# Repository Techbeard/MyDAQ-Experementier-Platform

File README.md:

# MyDAQ-Experementier-Platform
Studentisches Projekt mit dme MY DAQ

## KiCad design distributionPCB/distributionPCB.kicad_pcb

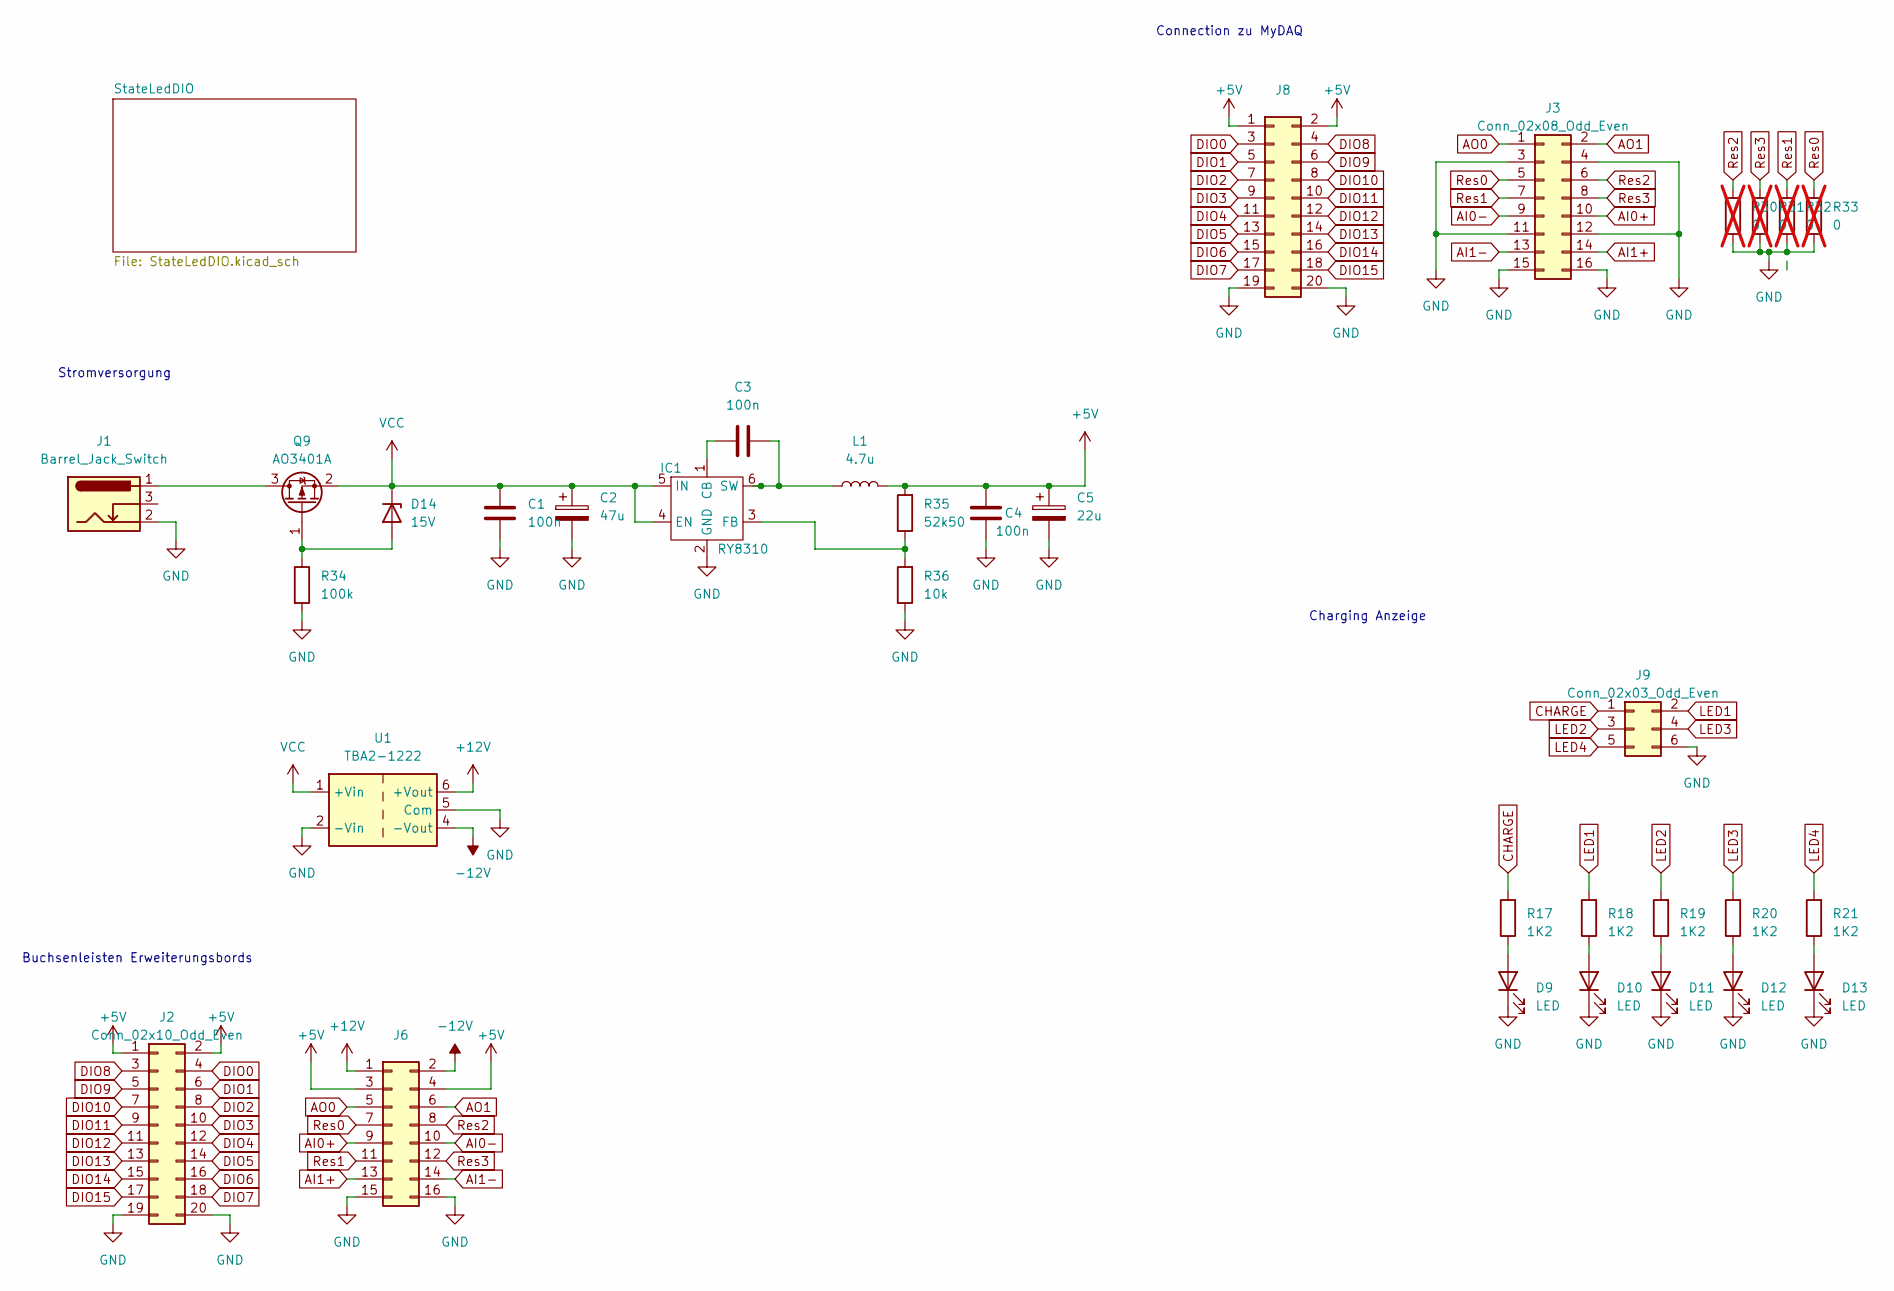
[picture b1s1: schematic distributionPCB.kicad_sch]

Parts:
C1, C3, C4: 100n; C_0402_1005Metric
C2: 47u; CP_Elec_5x5.4
C5: 22u; CP_Elec_5x5.4
D9, D10, D11, D12, D13: LED; LED_0805_2012Metric
D14: 15V; D_0402_1005Metric
IC1: RY8310; SOT-23-6
J1: Barrel_Jack_Switch; BarrelJack_10A
J2: Conn_02x10_Odd_Even; PinSocket_2x10_P2.54mm_Vertical
J3: Conn_02x08_Odd_Even; IDC-Header_2x08_P2.54mm_Vertical_SMD
J6: Conn_02x08_Odd_Even; PinSocket_2x08_P2.54mm_Vertical
J8: Conn_02x10_Odd_Even; IDC-Header_2x10_P2.54mm_Vertical_SMD
J9: Conn_02x03_Odd_Even; IDC-Header_2x03_P2.54mm_Vertical_SMD
L1: 4.7u; L_0630
Q9: AO3401A; SOT-23
R17, R18, R19, R20, R21: 1K2; R_0603_1608Metric
R30, R31, R32, R33: 0; R_0603_1608Metric; not fitted
R34: 100k; R_0402_1005Metric
R35: 52k50; R_0402_1005Metric
R36: 10k; R_0402_1005Metric
U1: TBA2-1222; Converter_DCDC_TRACO_TBA2-xxxx_Dual_THT

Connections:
+5V: C4.1, C5.1, J2.1, J2.2, J6.3, J6.4, J8.1, J8.2, L1.2, R35.2; also elsewhere on the board
+12V: J6.1, U1.6 (+Vout)
-12V: J6.2, U1.4 (-Vout)
AI0+: J3.10, J6.9
AI0-: J3.9, J6.10
AI1+: J3.14, J6.13
AI1-: J3.13, J6.14
AO0: J3.1, J6.5
AO1: J3.2, J6.6
CHARGE: J9.1, R17.2
DIO0: J2.4, J8.3; also elsewhere on the board
DIO1: J2.6, J8.5; also elsewhere on the board
DIO2: J2.8, J8.7; also elsewhere on the board
DIO3: J2.10, J8.9; also elsewhere on the board
DIO4: J2.12, J8.11; also elsewhere on the board
DIO5: J2.14, J8.13; also elsewhere on the board
DIO6: J2.16, J8.15; also elsewhere on the board
DIO7: J2.18, J8.17; also elsewhere on the board
DIO8: J2.3, J8.4
DIO9: J2.5, J8.6
DIO10: J2.7, J8.8
DIO11: J2.9, J8.10
DIO12: J2.11, J8.12
DIO13: J2.13, J8.14
DIO14: J2.15, J8.16
DIO15: J2.17, J8.18
GND: C1.2, C2.2, C4.2, C5.2, D9.1 (K), D10.1 (K), D11.1 (K), D12.1 (K), D13.1 (K), IC1.2 (GND), J1.2, J2.19, J2.20, J3.3, J3.4, J3.11, J3.12, J3.15, J3.16, J6.15, J6.16, J8.19, J8.20, J9.6, R30.1, R31.1, R32.1, R33.1, R34.2, R36.1, U1.2 (-Vin), U1.5 (Com); also elsewhere on the board
LED1: J9.2, R18.2
LED2: J9.3, R19.2
LED3: J9.4, R20.2
LED4: J9.5, R21.2
unnamed: D9.2 (A), R17.1
unnamed: D10.2 (A), R18.1
unnamed: D11.2 (A), R19.1
unnamed: D12.2 (A), R20.1
unnamed: D13.2 (A), R21.1
unnamed: D14.2 (A), Q9.1 (G), R34.1
unnamed: C3.1, IC1.1 (CB)
unnamed: IC1.3 (FB), R35.1, R36.2
unnamed: C3.2, IC1.6 (SW), L1.1
unnamed: J1.1, Q9.3 (D)
Res0: J3.5, J6.7, R33.2
Res1: J3.7, J6.11, R32.2
Res2: J3.6, J6.8, R30.2
Res3: J3.8, J6.12, R31.2
VCC: C1.1, C2.1, D14.1 (K), IC1.4 (EN), IC1.5 (IN), Q9.2 (S), U1.1 (+Vin)

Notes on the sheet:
Buchsenleisten Erweiterungsbords
Stromversorgung
Charging Anzeige
Connection zu MyDAQ

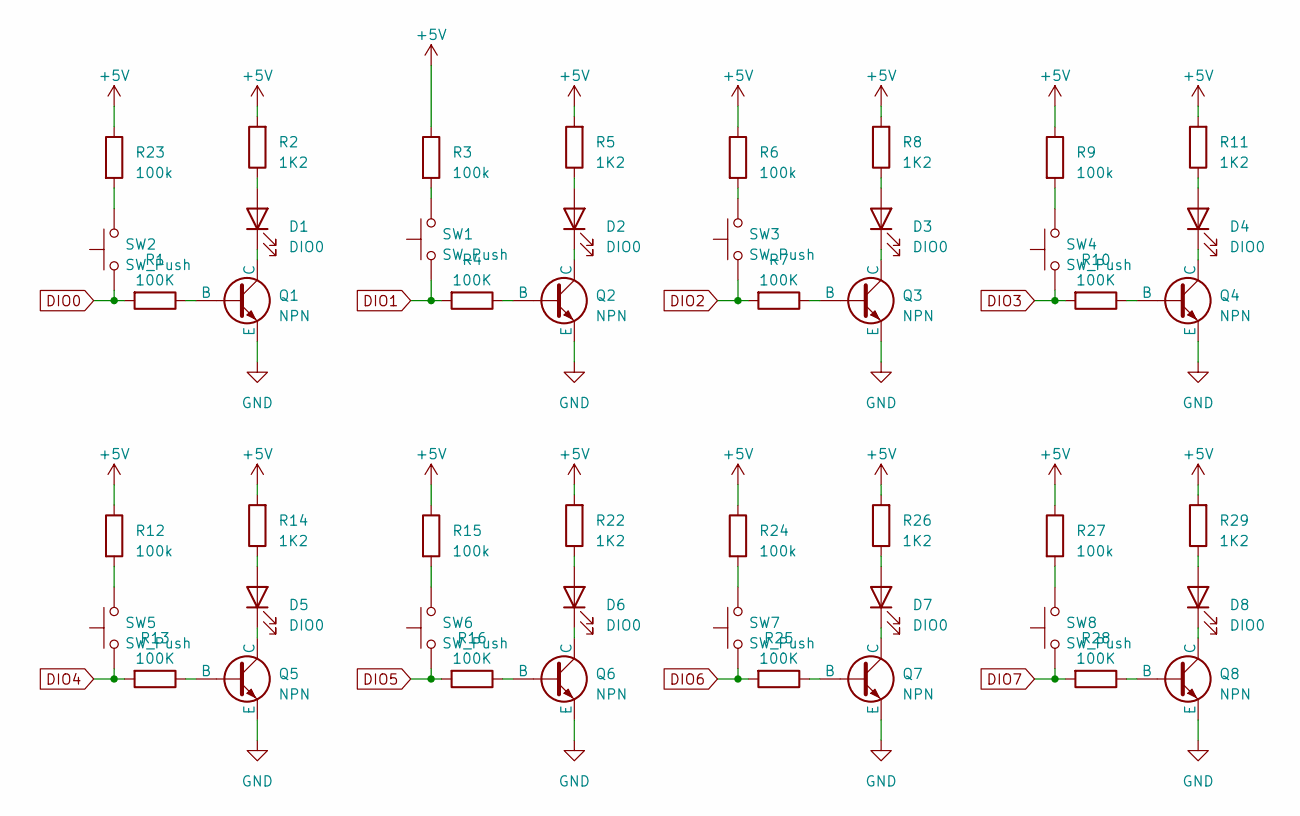
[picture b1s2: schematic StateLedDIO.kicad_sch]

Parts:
D1, D2, D3, D4, D5, D6, D7, D8: DIO0; LED_0805_2012Metric
Q1, Q2, Q3, Q4, Q5, Q6, Q7, Q8: NPN; TSOT-23
R1, R4, R7, R10, R13, R16, R25, R28: 100K; R_0603_1608Metric
R2, R5, R8, R11, R14, R22, R26, R29: 1K2; R_0603_1608Metric
R3, R6, R9, R12, R15, R23, R24, R27: 100k; R_0603_1608Metric
SW1, SW2, SW3, SW4, SW5, SW6, SW7, SW8: SW_Push; SW_SPST_SKQG_WithStem

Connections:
+5V: R2.2, R3.1, R5.2, R6.1, R8.2, R9.1, R11.2, R12.1, R14.2, R15.1, R22.2, R23.1, R24.1, R26.2, R27.1, R29.2; also elsewhere on the board
DIO0: R1.2, SW2.1; also elsewhere on the board
DIO1: R4.2, SW1.1; also elsewhere on the board
DIO2: R7.2, SW3.1; also elsewhere on the board
DIO3: R10.2, SW4.1; also elsewhere on the board
DIO4: R13.2, SW5.1; also elsewhere on the board
DIO5: R16.2, SW6.1; also elsewhere on the board
DIO6: R25.2, SW7.1; also elsewhere on the board
DIO7: R28.2, SW8.1; also elsewhere on the board
GND: Q1.3 (E), Q2.3 (E), Q3.3 (E), Q4.3 (E), Q5.3 (E), Q6.3 (E), Q7.3 (E), Q8.3 (E); also elsewhere on the board
unnamed: D1.2 (A), R2.1
unnamed: D1.1 (K), Q1.1 (C)
unnamed: D2.2 (A), R5.1
unnamed: D2.1 (K), Q2.1 (C)
unnamed: D3.2 (A), R8.1
unnamed: D3.1 (K), Q3.1 (C)
unnamed: D4.2 (A), R11.1
unnamed: D4.1 (K), Q4.1 (C)
unnamed: D5.2 (A), R14.1
unnamed: D5.1 (K), Q5.1 (C)
unnamed: D6.2 (A), R22.1
unnamed: D6.1 (K), Q6.1 (C)
unnamed: D7.2 (A), R26.1
unnamed: D7.1 (K), Q7.1 (C)
unnamed: D8.2 (A), R29.1
unnamed: D8.1 (K), Q8.1 (C)
unnamed: Q1.2 (B), R1.1
unnamed: Q2.2 (B), R4.1
unnamed: Q3.2 (B), R7.1
unnamed: Q4.2 (B), R10.1
unnamed: Q5.2 (B), R13.1
unnamed: Q6.2 (B), R16.1
unnamed: Q7.2 (B), R25.1
unnamed: Q8.2 (B), R28.1
unnamed: R3.2, SW1.2
unnamed: R6.2, SW3.2
unnamed: R9.2, SW4.2
unnamed: R12.2, SW5.2
unnamed: R15.2, SW6.2
unnamed: R23.2, SW2.2
unnamed: R24.2, SW7.2
unnamed: R27.2, SW8.2

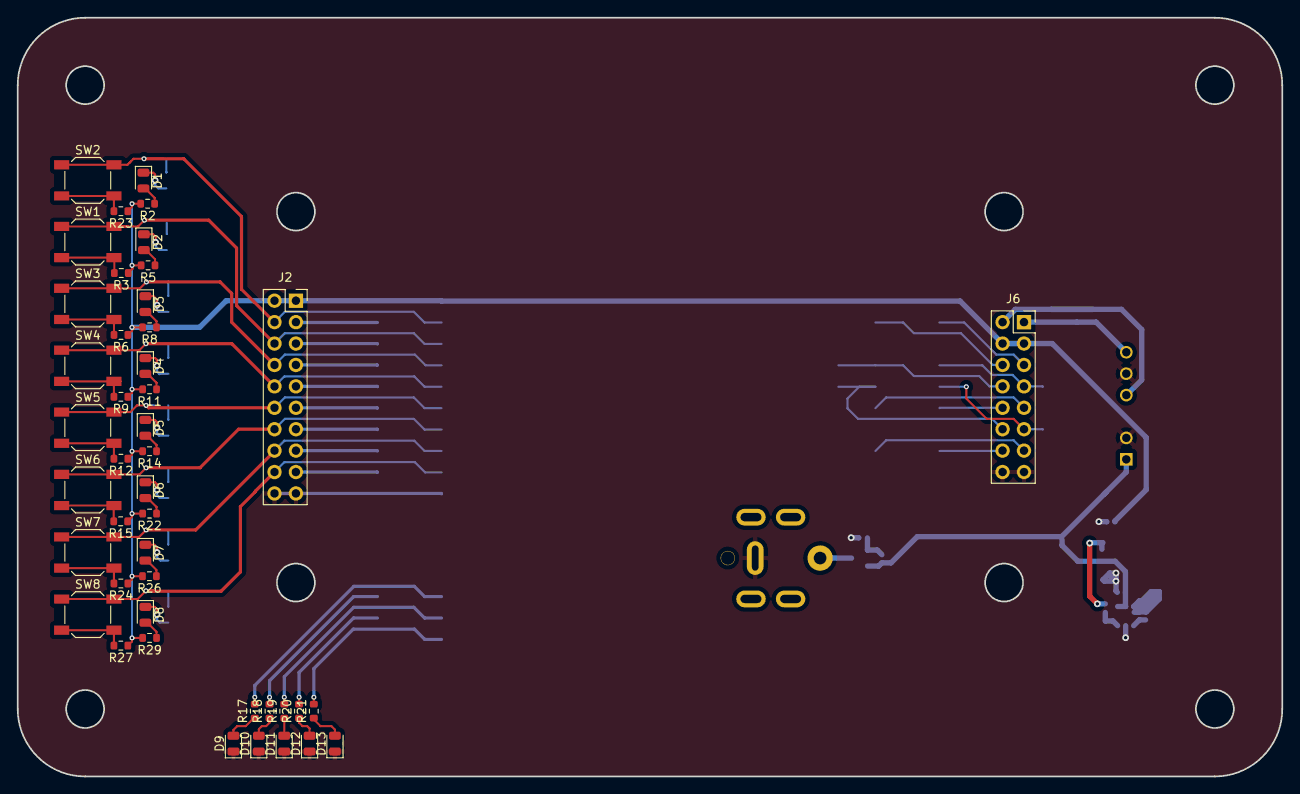
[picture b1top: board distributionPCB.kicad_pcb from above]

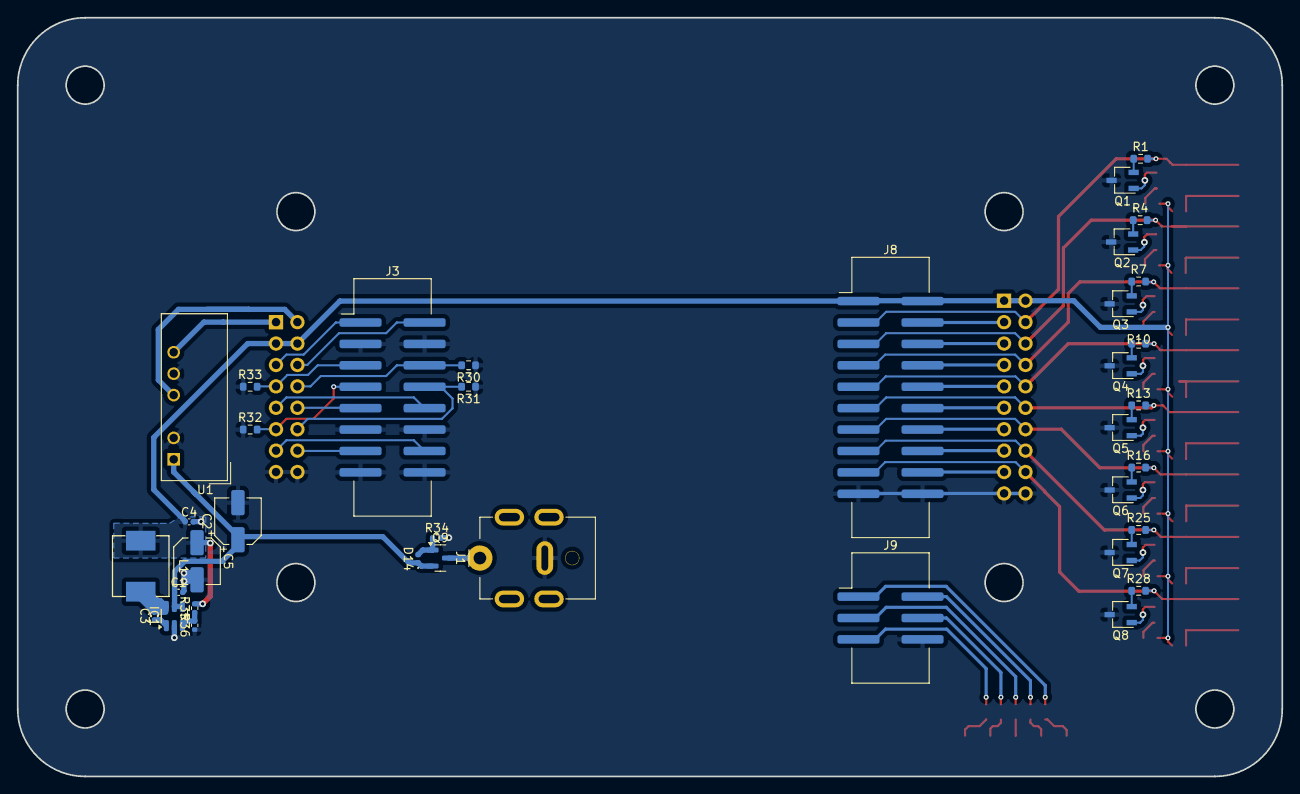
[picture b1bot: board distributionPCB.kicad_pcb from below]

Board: 2 copper layers, 150.0 x 90.0 mm, 81 parts (37 on the bottom side), 78 nets.

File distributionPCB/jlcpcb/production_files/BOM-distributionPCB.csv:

Comment,Designator,Footprint,LCSC
1K2,R5,R_0603_1608Metric,
1K2,R18,R_0603_1608Metric,
Conn_02x08_Odd_Even,J6,PinSocket_2x08_P2.54mm_Vertical,
LED,D13,LED_0805_2012Metric,
DIO0,D3,LED_0805_2012Metric,
SW_Push,SW7,SW_SPST_SKQG_WithStem,
1K2,R20,R_0603_1608Metric,
SW_Push,SW8,SW_SPST_SKQG_WithStem,
SW_Push,SW6,SW_SPST_SKQG_WithStem,
1K2,R26,R_0603_1608Metric,
DIO0,D2,LED_0805_2012Metric,
100k,R12,R_0603_1608Metric,
DIO0,D1,LED_0805_2012Metric,
1K2,R22,R_0603_1608Metric,
1K2,R21,R_0603_1608Metric,
LED,D9,LED_0805_2012Metric,
SW_Push,SW2,SW_SPST_SKQG_WithStem,
100k,R6,R_0603_1608Metric,
1K2,R17,R_0603_1608Metric,
100k,R23,R_0603_1608Metric,
100k,R24,R_0603_1608Metric,
LED,D10,LED_0805_2012Metric,
100k,R15,R_0603_1608Metric,
LED,D11,LED_0805_2012Metric,
1K2,R2,R_0603_1608Metric,
SW_Push,SW5,SW_SPST_SKQG_WithStem,
LED,D12,LED_0805_2012Metric,
SW_Push,SW1,SW_SPST_SKQG_WithStem,
DIO0,D6,LED_0805_2012Metric,
SW_Push,SW3,SW_SPST_SKQG_WithStem,
Conn_02x10_Odd_Even,J2,PinSocket_2x10_P2.54mm_Vertical,
1K2,R29,R_0603_1608Metric,
DIO0,D7,LED_0805_2012Metric,
1K2,R11,R_0603_1608Metric,
DIO0,D5,LED_0805_2012Metric,
SW_Push,SW4,SW_SPST_SKQG_WithStem,
1K2,R14,R_0603_1608Metric,
1K2,R19,R_0603_1608Metric,
100k,R27,R_0603_1608Metric,
100k,R9,R_0603_1608Metric,
1K2,R8,R_0603_1608Metric,
100k,R3,R_0603_1608Metric,
DIO0,D8,LED_0805_2012Metric,
DIO0,D4,LED_0805_2012Metric,
100K,R25,R_0603_1608Metric,
100K,R7,R_0603_1608Metric,
0,R30,R_0603_1608Metric,
NPN,Q5,TSOT-23,
100K,R1,R_0603_1608Metric,
100K,R13,R_0603_1608Metric,
Barrel_Jack_Switch,J1,BarrelJack_10A,
100n,C1,C_0402_1005Metric,
100K,R16,R_0603_1608Metric,
0,R33,R_0603_1608Metric,
TBA2-1222,U1,Converter_DCDC_TRACO_TBA2-xxxx_Dual_THT,
Conn_02x10_Odd_Even,J8,IDC-Header_2x10_P2.54mm_Vertical_SMD,
47u,C2,CP_Elec_5x5.4,
100n,C4,C_0402_1005Metric,
NPN,Q3,TSOT-23,
100n,C3,C_0402_1005Metric,
100k,R34,R_0402_1005Metric,
15V,D14,D_0402_1005Metric,
Conn_02x03_Odd_Even,J9,IDC-Header_2x03_P2.54mm_Vertical_SMD,
NPN,Q8,TSOT-23,
0,R32,R_0603_1608Metric,
NPN,Q4,TSOT-23,
100K,R28,R_0603_1608Metric,
RY8310,IC1,SOT-23-6,
100K,R4,R_0603_1608Metric,
100K,R10,R_0603_1608Metric,
4.7u,L1,L_0630,
AO3401A,Q9,SOT-23,
NPN,Q6,TSOT-23,
0,R31,R_0603_1608Metric,
Conn_02x08_Odd_Even,J3,IDC-Header_2x08_P2.54mm_Vertical_SMD,
NPN,Q1,TSOT-23,
NPN,Q2,TSOT-23,
NPN,Q7,TSOT-23,
10k,R36,R_0402_1005Metric,
52k50,R35,R_0402_1005Metric,
22u,C5,CP_Elec_5x5.4,

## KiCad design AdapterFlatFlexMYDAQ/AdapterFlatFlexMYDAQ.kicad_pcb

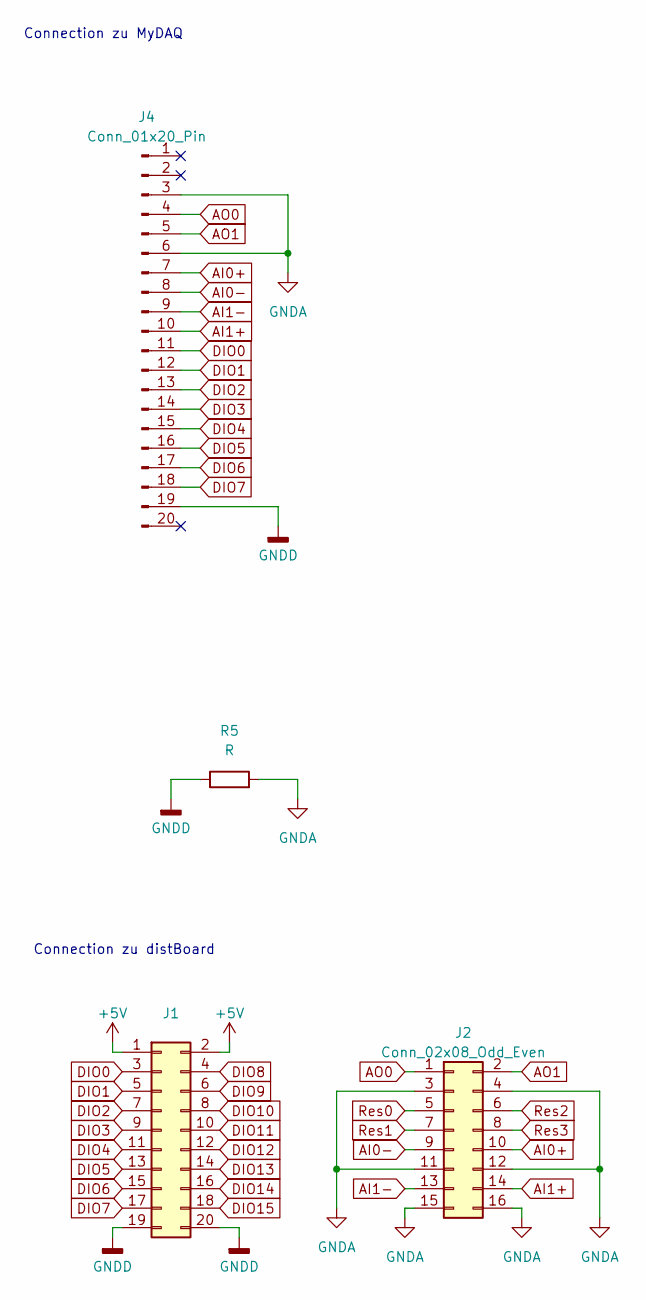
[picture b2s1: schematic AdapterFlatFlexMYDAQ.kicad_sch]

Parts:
J1: Conn_02x10_Odd_Even; IDC-Header_2x10_P2.54mm_Vertical_SMD
J2: Conn_02x08_Odd_Even; IDC-Header_2x08_P2.54mm_Vertical_SMD
J4: Conn_01x20_Pin; OSTV7203151
R5: R; R_0603_1608Metric

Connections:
+5V: J1.1, J1.2
AI0+: J2.10, J4.7
AI0-: J2.9, J4.8
AI1+: J2.14, J4.10
AI1-: J2.13, J4.9
AO0: J2.1, J4.4
AO1: J2.2, J4.5
DIO0: J1.3, J4.11
DIO1: J1.5, J4.12
DIO2: J1.7, J4.13
DIO3: J1.9, J4.14
DIO4: J1.11, J4.15
DIO5: J1.13, J4.16
DIO6: J1.15, J4.17
DIO7: J1.17, J4.18
DIO8: J1.4
DIO9: J1.6
DIO10: J1.8
DIO11: J1.10
DIO12: J1.12
DIO13: J1.14
DIO14: J1.16
DIO15: J1.18
GNDA: J2.3, J2.4, J2.11, J2.12, J2.15, J2.16, J4.3, J4.6, R5.2
GNDD: J1.19, J1.20, J4.19, R5.1
Res0: J2.5
Res1: J2.7
Res2: J2.6
Res3: J2.8

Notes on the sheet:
Connection zu distBoard
Connection zu MyDAQ

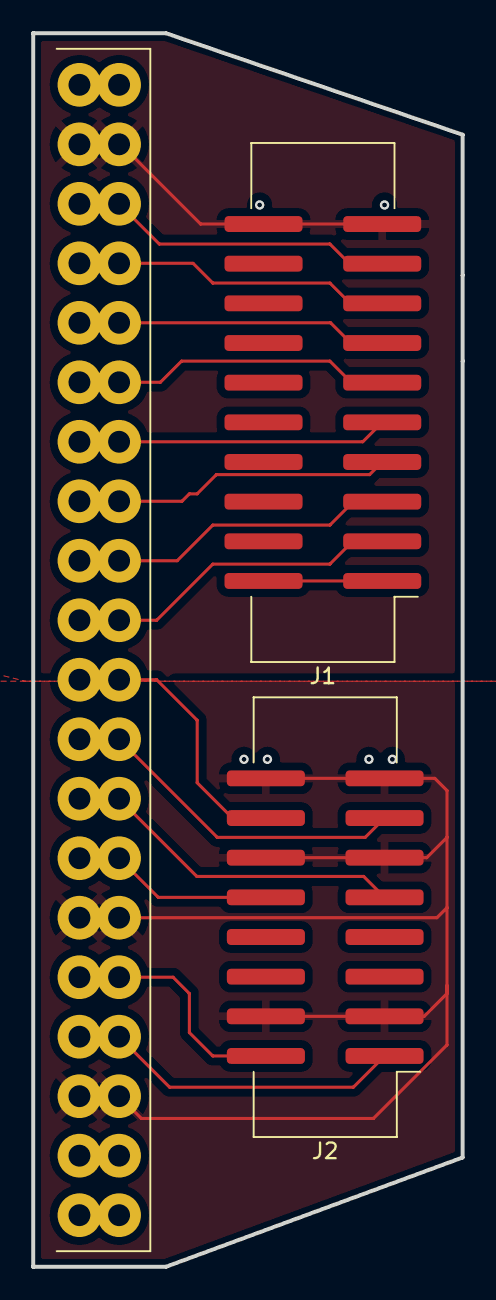
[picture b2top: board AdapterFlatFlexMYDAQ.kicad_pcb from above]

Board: 2 copper layers, 27.5 x 79.0 mm, 4 parts (1 on the bottom side), 17 nets.

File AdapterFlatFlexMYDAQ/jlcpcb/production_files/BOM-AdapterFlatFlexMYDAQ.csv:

Comment,Designator,Footprint,LCSC
Conn_02x10_Odd_Even,J1,IDC-Header_2x10_P2.54mm_Vertical_SMD,
Conn_02x08_Odd_Even,J2,IDC-Header_2x08_P2.54mm_Vertical_SMD,
Conn_01x20_Pin,J4,OSTV7203151,
R,R5,R_0603_1608Metric,

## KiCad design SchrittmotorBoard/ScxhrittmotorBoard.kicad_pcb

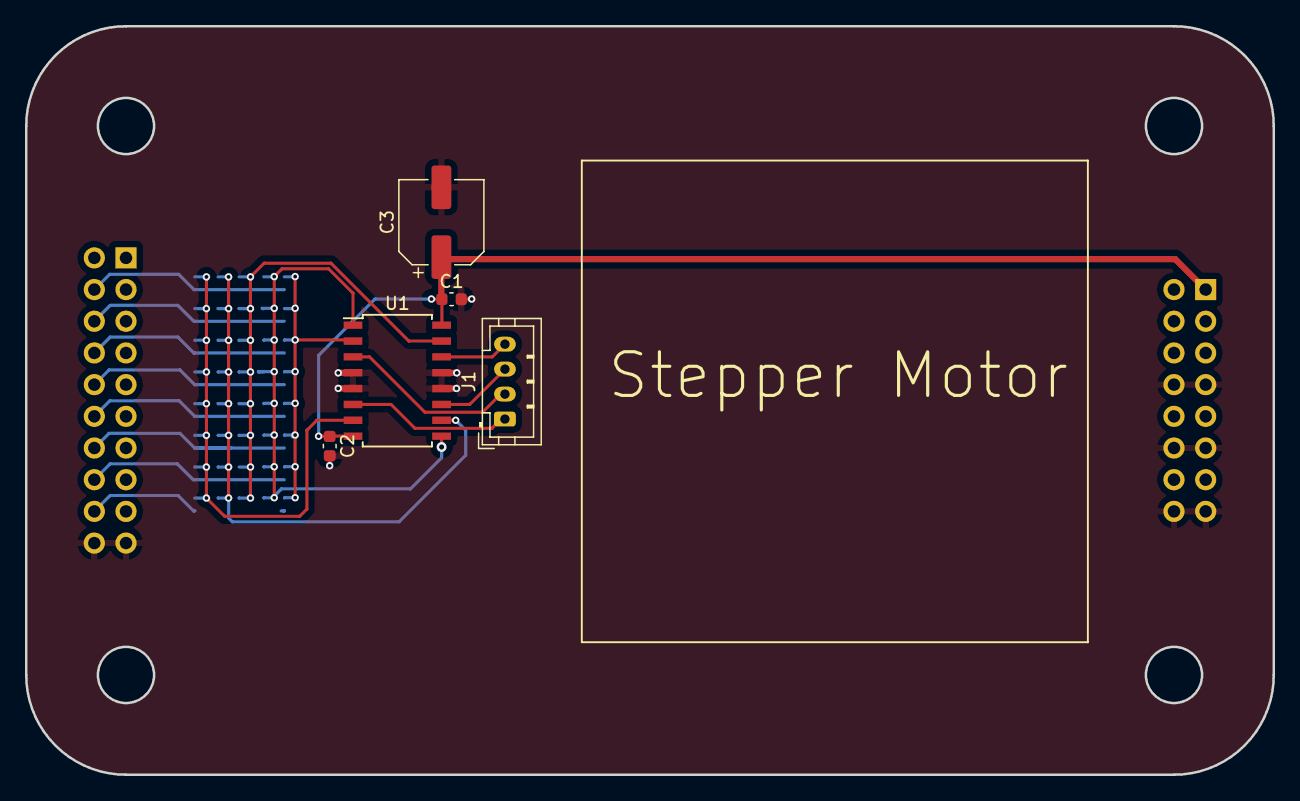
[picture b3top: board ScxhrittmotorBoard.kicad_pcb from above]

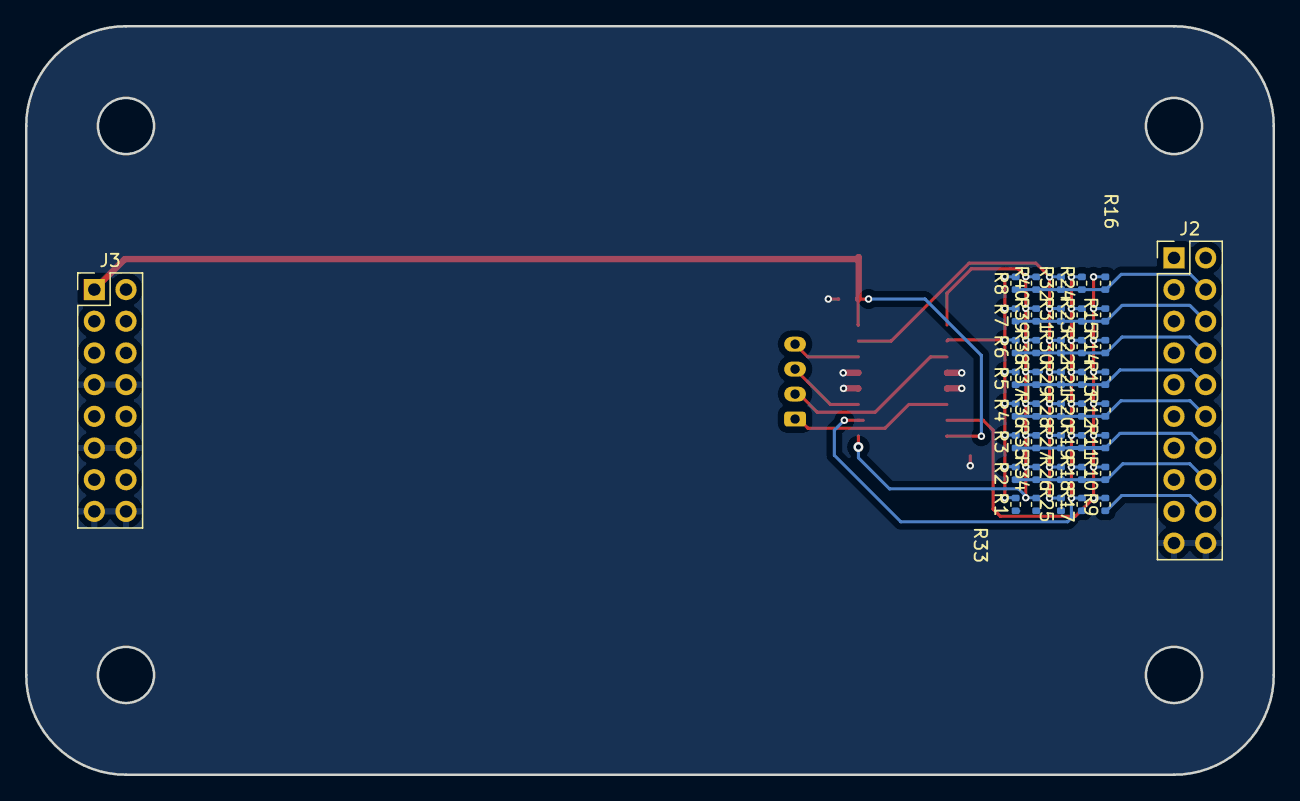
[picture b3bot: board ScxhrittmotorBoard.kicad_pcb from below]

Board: 2 copper layers, 100.0 x 60.0 mm, 47 parts (42 on the bottom side), 19 nets.

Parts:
C1, C2: 100n; C_0603_1608Metric
C3: 4u7; CP_Elec_6.3x5.2
J1: Conn_01x04_Socket; JST_PH_B4B-PH-K_1x04_P2.00mm_Vertical
J2: Conn_02x10_Odd_Even; PinHeader_2x10_P2.54mm_Vertical
J3: Conn_02x08_Odd_Even; PinHeader_2x08_P2.54mm_Vertical
R1, R2, R3, R4, R5, R6, R7, R8, R9, R10, R11, R12, R13, R14, R15, R16, R17, R18, R19, R20, R21, R22, R23, R24, R25, R26, R27, R28, R29, R30, R31, R32, R33, R34, R35, R36, R37, R38, R39, R40: 0; R_0402_1005Metric
U1: L293D; SOIC-16W_5.3x10.2mm_P1.27mm

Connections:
+12V: C1.1, C2.1, C3.1, J3.1, U1.8 (VCC2), U1.16 (VCC1)
DIO0: J2.4, R8.1, R16.1, R24.1, R32.1, R40.1
DIO1: J2.6, R7.1, R15.1, R23.1, R31.1, R39.1
DIO2: J2.8, R6.1, R14.1, R22.1, R30.1, R38.1
DIO3: J2.10, R5.1, R13.1, R21.1, R29.1, R37.1
DIO4: J2.12, R4.1, R12.1, R20.1, R28.1, R36.1
DIO5: J2.14, R3.1, R11.1, R19.1, R27.1, R35.1
DIO6: J2.16, R2.1, R10.1, R18.1, R26.1, R34.1
DIO7: J2.18, R1.1, R9.1, R17.1, R25.1, R33.1
GND: C1.2, C2.2, C3.2, J2.19, J2.20, J3.7, J3.8, J3.11, J3.12, J3.15, J3.16, U1.4 (GND), U1.5 (GND), U1.12 (GND), U1.13 (GND)
Motor_1A: R1.2, R2.2, R3.2, R4.2, R5.2, R6.2, R7.2, R8.2, U1.2 (1A)
Motor_2A: R9.2, R10.2, R11.2, R12.2, R13.2, R14.2, R15.2, R16.2, U1.7 (2A)
Motor_3A: R17.2, R18.2, R19.2, R20.2, R21.2, R22.2, R23.2, R24.2, U1.10 (3A)
Motor_4A: R25.2, R26.2, R27.2, R28.2, R29.2, R30.2, R31.2, R32.2, U1.15 (4A)
Motor_EN: R33.2, R34.2, R35.2, R36.2, R37.2, R38.2, R39.2, R40.2, U1.1 (EN1,2), U1.9 (EN3,4)
unnamed: J1.1, U1.6 (2Y)
unnamed: J1.2, U1.3 (1Y)
unnamed: J1.3, U1.11 (3Y)
unnamed: J1.4, U1.14 (4Y)

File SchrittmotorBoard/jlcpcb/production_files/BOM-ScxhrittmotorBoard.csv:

Comment,Designator,Footprint,LCSC
L293D,U1,SOIC-16W_5.3x10.2mm_P1.27mm,
100n,C1,C_0603_1608Metric,
Conn_01x04_Socket,J1,JST_PH_B4B-PH-K_1x04_P2.00mm_Vertical,
100n,C2,C_0603_1608Metric,
4u7,C3,CP_Elec_6.3x5.2,
0,R4,R_0402_1005Metric,
0,R10,R_0402_1005Metric,
0,R25,R_0402_1005Metric,
0,R22,R_0402_1005Metric,
0,R6,R_0402_1005Metric,
0,R1,R_0402_1005Metric,
0,R12,R_0402_1005Metric,
0,R2,R_0402_1005Metric,
0,R34,R_0402_1005Metric,
0,R15,R_0402_1005Metric,
0,R37,R_0402_1005Metric,
0,R21,R_0402_1005Metric,
0,R13,R_0402_1005Metric,
0,R29,R_0402_1005Metric,
0,R33,R_0402_1005Metric,
0,R9,R_0402_1005Metric,
0,R30,R_0402_1005Metric,
0,R17,R_0402_1005Metric,
0,R5,R_0402_1005Metric,
0,R27,R_0402_1005Metric,
0,R18,R_0402_1005Metric,
0,R39,R_0402_1005Metric,
0,R7,R_0402_1005Metric,
0,R35,R_0402_1005Metric,
Conn_02x08_Odd_Even,J3,PinHeader_2x08_P2.54mm_Vertical,
0,R11,R_0402_1005Metric,
0,R3,R_0402_1005Metric,
0,R40,R_0402_1005Metric,
0,R14,R_0402_1005Metric,
0,R20,R_0402_1005Metric,
0,R23,R_0402_1005Metric,
0,R24,R_0402_1005Metric,
0,R36,R_0402_1005Metric,
Conn_02x10_Odd_Even,J2,PinHeader_2x10_P2.54mm_Vertical,
0,R28,R_0402_1005Metric,
0,R31,R_0402_1005Metric,
0,R8,R_0402_1005Metric,
0,R16,R_0402_1005Metric,
0,R19,R_0402_1005Metric,
0,R26,R_0402_1005Metric,
0,R32,R_0402_1005Metric,
0,R38,R_0402_1005Metric,

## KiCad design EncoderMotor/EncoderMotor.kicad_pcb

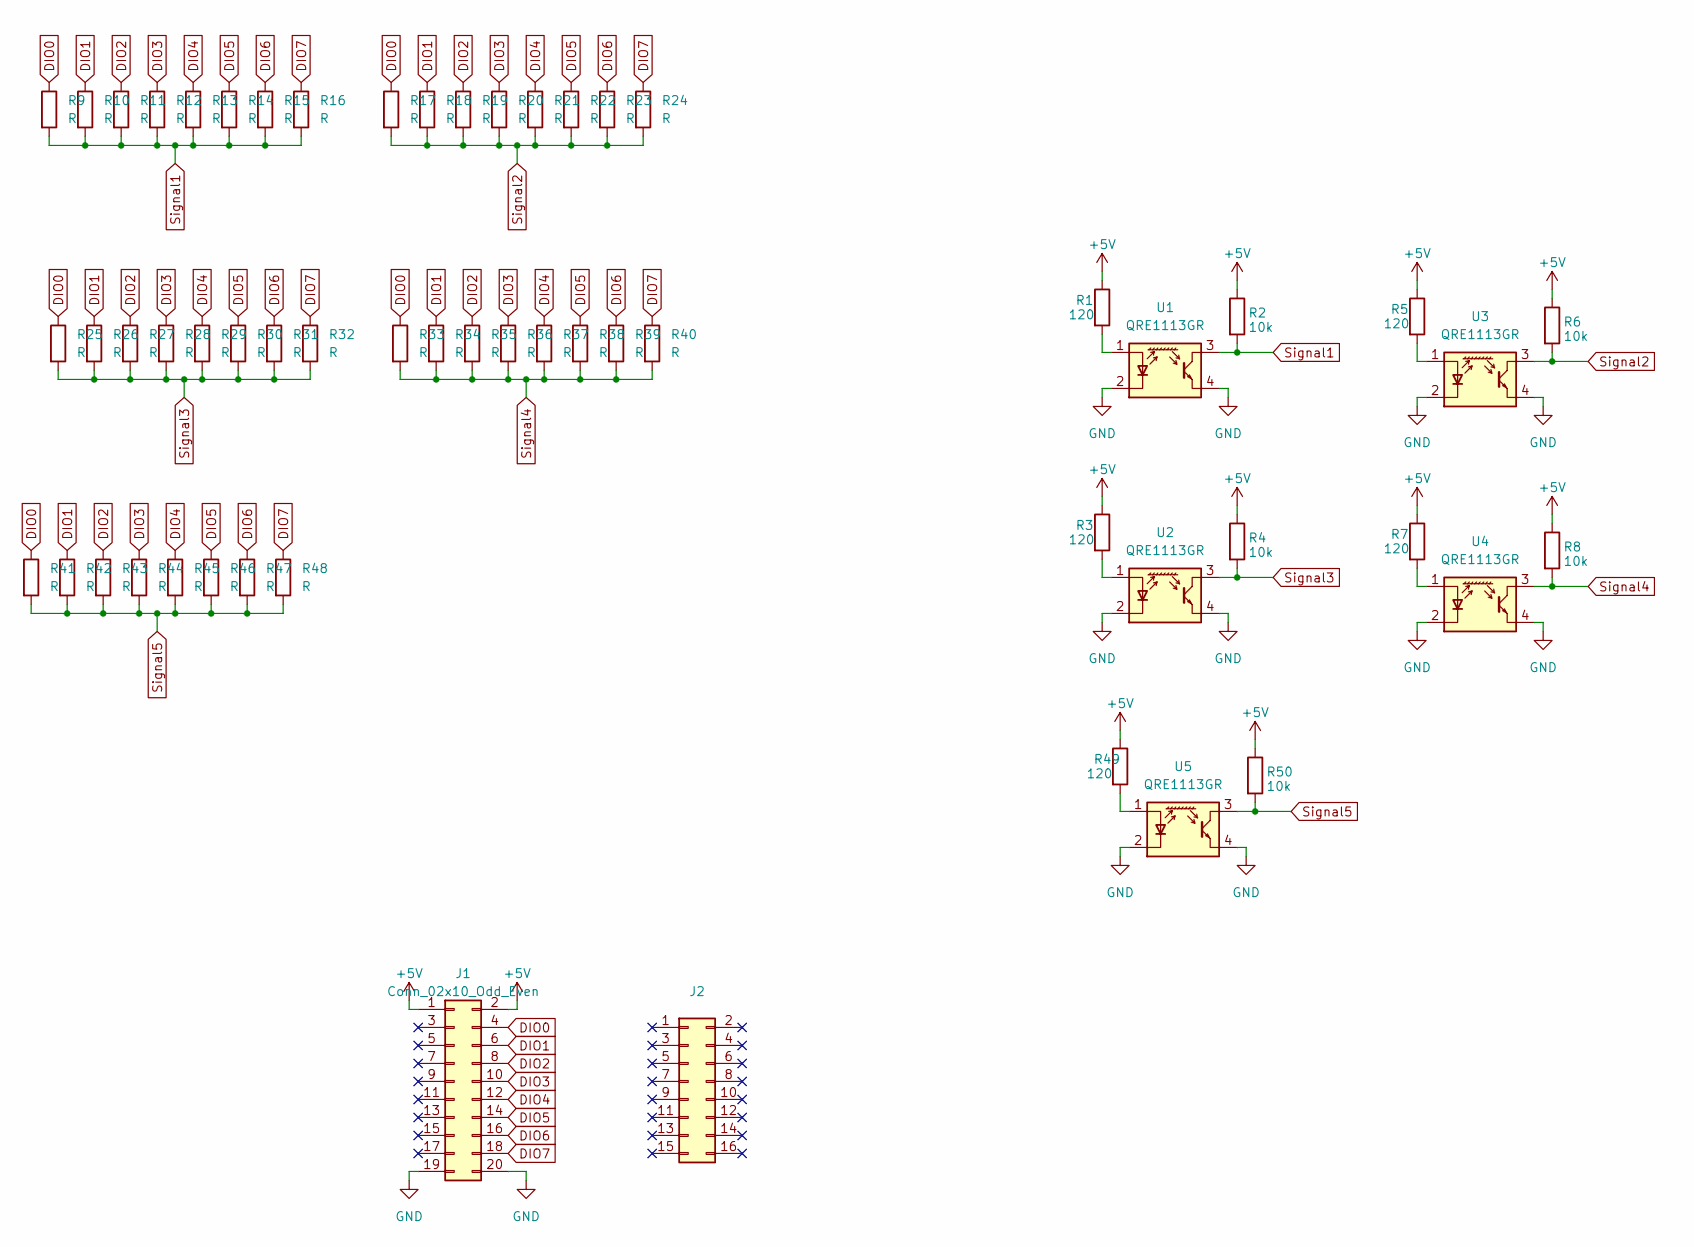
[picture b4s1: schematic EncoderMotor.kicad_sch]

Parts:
J1: Conn_02x10_Odd_Even; PinSocket_2x10_P2.54mm_Vertical
J2: Conn_02x08_Odd_Even; PinSocket_2x08_P2.54mm_Vertical
R1, R3, R5, R7, R49: 120; C_0603_1608Metric
R2, R4, R6, R50: 10k; C_0603_1608Metric
R8: 10k; R_0402_1005Metric
R9, R10, R11, R12, R13, R14, R15, R16, R17, R18, R19, R20, R21, R22, R23, R24, R25, R26, R27, R28, R29, R30, R31, R32, R33, R34, R35, R36, R37, R38, R39, R40, R41, R42, R43, R44, R45, R46, R47, R48: R; R_0402_1005Metric
U1, U2, U3, U4, U5: QRE1113GR; OnSemi_CASE100CY

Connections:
+5V: J1.1, J1.2, R1.1, R2.1, R3.1, R4.1, R5.1, R6.1, R7.1, R8.1, R49.1, R50.1
DIO0: J1.4, R9.1, R17.1, R25.1, R33.1, R41.1
DIO1: J1.6, R10.1, R18.1, R26.1, R34.1, R42.1
DIO2: J1.8, R11.1, R19.1, R27.1, R35.1, R43.1
DIO3: J1.10, R12.1, R20.1, R28.1, R36.1, R44.1
DIO4: J1.12, R13.1, R21.1, R29.1, R37.1, R45.1
DIO5: J1.14, R14.1, R22.1, R30.1, R38.1, R46.1
DIO6: J1.16, R15.1, R23.1, R31.1, R39.1, R47.1
DIO7: J1.18, R16.1, R24.1, R32.1, R40.1, R48.1
GND: J1.19, J1.20, U1.2 (K), U1.4, U2.2 (K), U2.4, U3.2 (K), U3.4, U4.2 (K), U4.4, U5.2 (K), U5.4
unnamed: R1.2, U1.1 (A)
unnamed: R3.2, U2.1 (A)
unnamed: R5.2, U3.1 (A)
unnamed: R7.2, U4.1 (A)
unnamed: R49.2, U5.1 (A)
Signal1: R2.2, R9.2, R10.2, R11.2, R12.2, R13.2, R14.2, R15.2, R16.2, U1.3
Signal2: R6.2, R17.2, R18.2, R19.2, R20.2, R21.2, R22.2, R23.2, R24.2, U3.3
Signal3: R4.2, R25.2, R26.2, R27.2, R28.2, R29.2, R30.2, R31.2, R32.2, U2.3
Signal4: R8.2, R33.2, R34.2, R35.2, R36.2, R37.2, R38.2, R39.2, R40.2, U4.3
Signal5: R41.2, R42.2, R43.2, R44.2, R45.2, R46.2, R47.2, R48.2, R50.2, U5.3

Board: 2 copper layers, 57 parts (40 on the bottom side), 20 nets, no tracks yet.

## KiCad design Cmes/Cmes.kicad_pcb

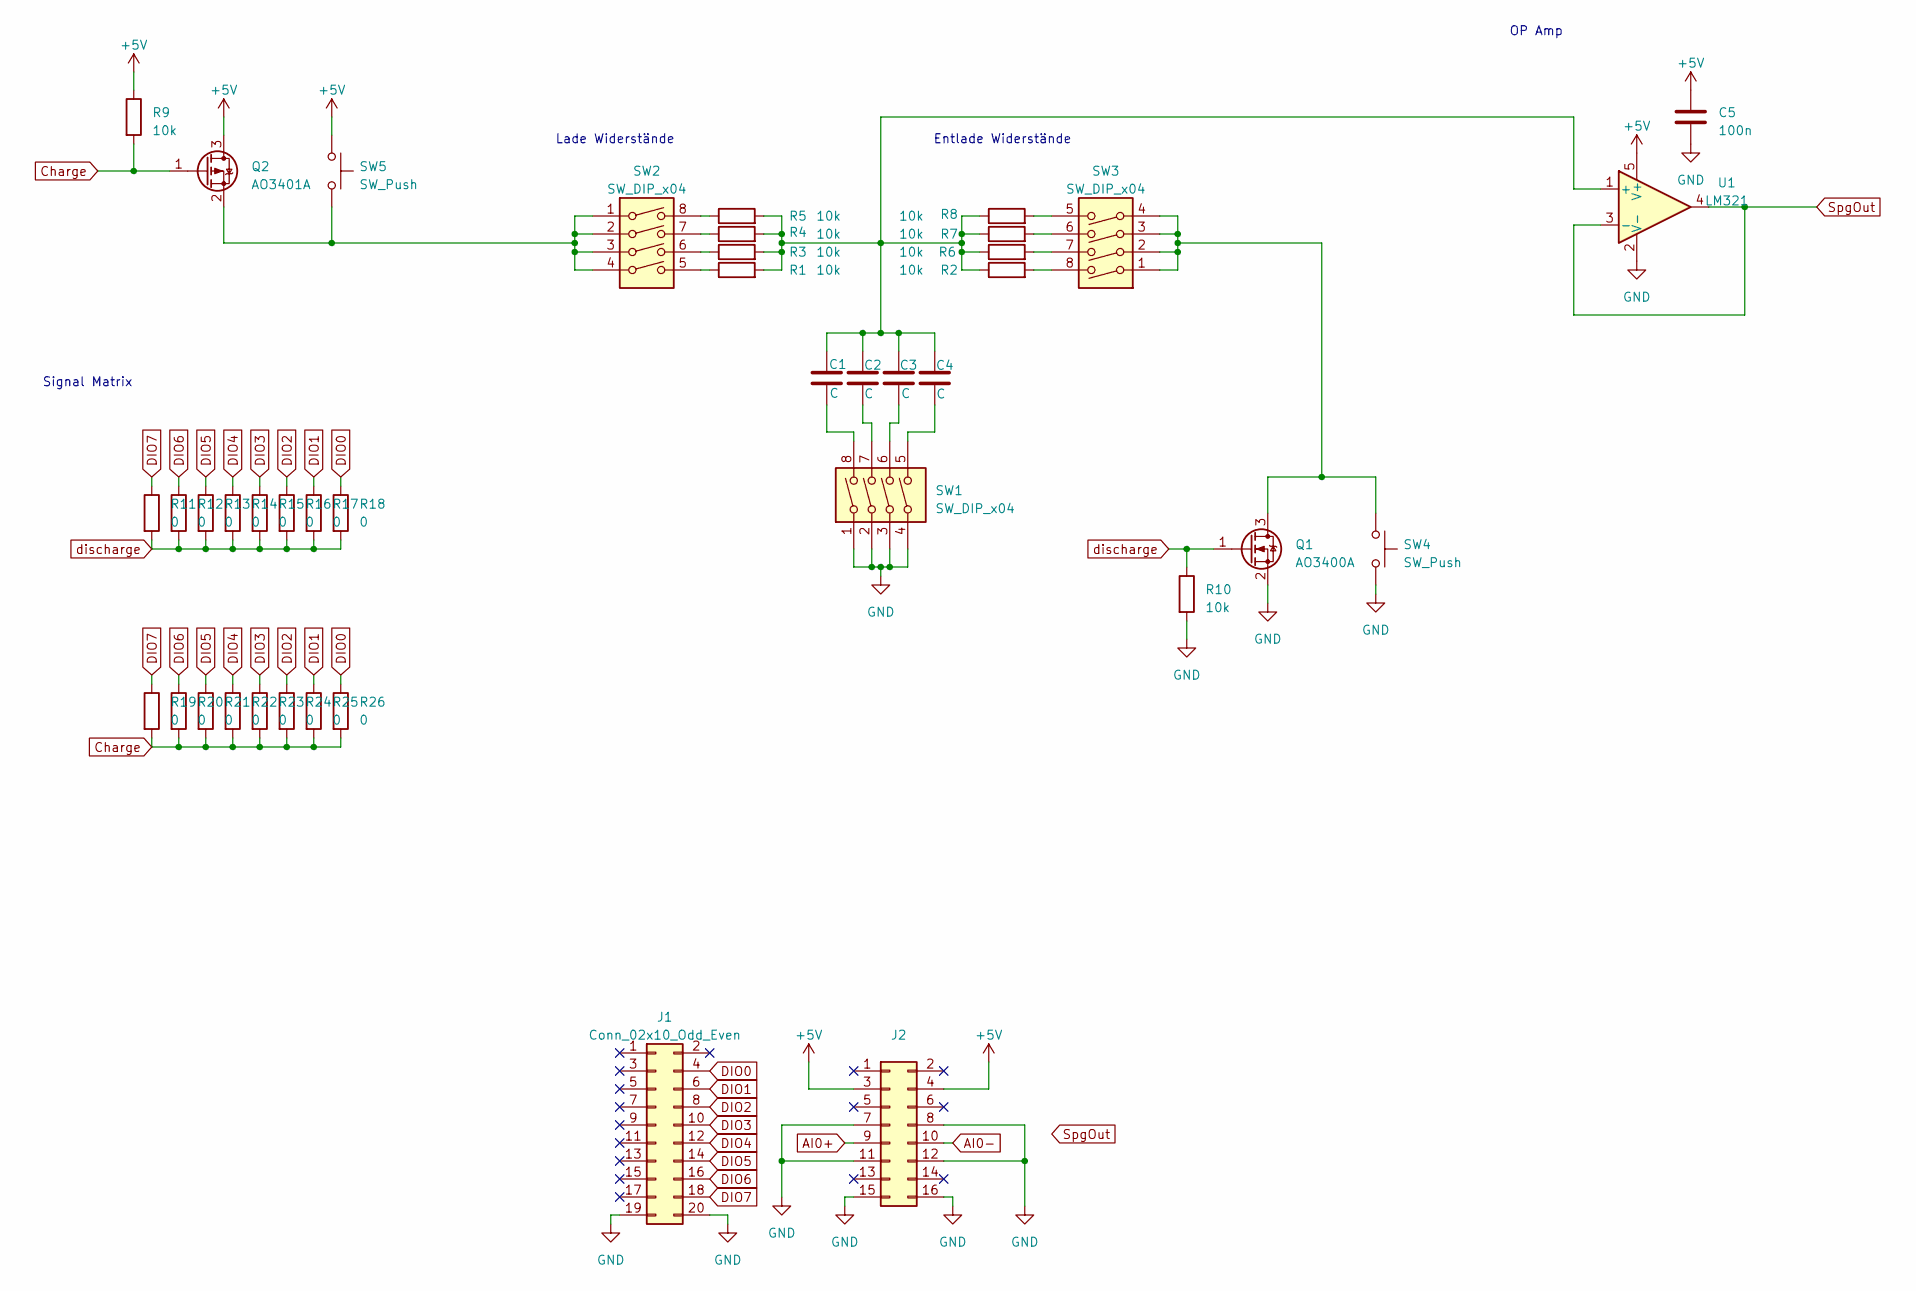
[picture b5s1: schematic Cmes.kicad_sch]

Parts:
C1, C2, C3, C4: C; C_0603_1608Metric
C5: 100n; C_0603_1608Metric
J1: Conn_02x10_Odd_Even; PinHeader_2x10_P2.54mm_Vertical
J2: Conn_02x08_Odd_Even; PinHeader_2x08_P2.54mm_Vertical
Q1: AO3400A; SOT-23
Q2: AO3401A; SOT-23
R1, R2, R3, R4, R5, R6, R7, R8, R9, R10: 10k; R_0603_1608Metric
R11, R12, R13, R14, R15, R16, R17, R18, R19, R20, R21, R22, R23, R24, R25, R26: 0; R_0402_1005Metric
SW1, SW2, SW3: SW_DIP_x04; SW-SMD_8P-L6.7-W5.4-P1.27-LS8.5
SW4, SW5: SW_Push; SW_SPST_SKQG_WithStem
U1: LM321; SOT-23-5

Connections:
+5V: C5.1, J2.3, J2.4, Q2.3 (D), R9.1, SW5.1, U1.5 (V+)
AI0+: J2.9
AI0-: J2.10
Charge: Q2.1 (G), R9.2, R19.2, R20.2, R21.2, R22.2, R23.2, R24.2, R25.2, R26.2
DIO0: J1.4, R18.1, R26.1
DIO1: J1.6, R17.1, R25.1
DIO2: J1.8, R16.1, R24.1
DIO3: J1.10, R15.1, R23.1
DIO4: J1.12, R14.1, R22.1
DIO5: J1.14, R13.1, R21.1
DIO6: J1.16, R12.1, R20.1
DIO7: J1.18, R11.1, R19.1
GND: C5.2, J1.19, J1.20, J2.7, J2.8, J2.11, J2.12, J2.15, J2.16, Q1.2 (S), R10.2, SW1.1, SW1.2, SW1.3, SW1.4, SW4.2, U1.2 (V-)
unnamed: C1.2, SW1.8
unnamed: C2.2, SW1.7
unnamed: C3.2, SW1.6
unnamed: C4.2, SW1.5
unnamed: Q1.3 (D), SW3.1, SW3.2, SW3.3, SW3.4, SW4.1
unnamed: Q2.2 (S), SW2.1, SW2.2, SW2.3, SW2.4, SW5.2
unnamed: R1.1, SW2.5
unnamed: R2.2, SW3.8
unnamed: R3.1, SW2.6
unnamed: R4.1, SW2.7
unnamed: R5.1, SW2.8
unnamed: R6.2, SW3.7
unnamed: R7.2, SW3.6
unnamed: R8.2, SW3.5
unnamed: C1.1, C2.1, C3.1, C4.1, R1.2, R2.1, R3.2, R4.2, R5.2, R6.1, R7.1, R8.1, U1.1 (+)
SpgOut: U1.3 (-), U1.4
discharge: Q1.1 (G), R10.1, R11.2, R12.2, R13.2, R14.2, R15.2, R16.2, R17.2, R18.2

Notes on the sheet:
Lade Widerstände
Signal Matrix
Entlade Widerstände
OP Amp
